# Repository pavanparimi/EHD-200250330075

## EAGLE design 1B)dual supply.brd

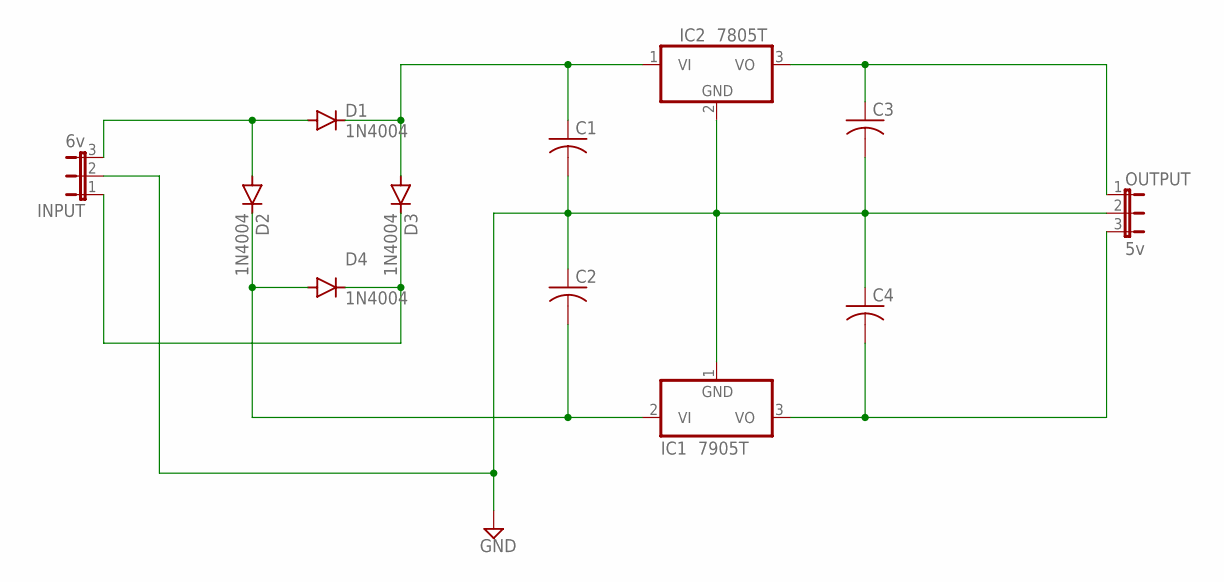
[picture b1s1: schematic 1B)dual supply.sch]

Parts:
C1, C2, C3, C4: C-US150-054X183; C150-054X183
D1, D2, D3, D4: 1N4004; DO41-10
IC1: 7905T; TO220H
IC2: 7805T; TO220H
INPUT: 6v; JP2
OUTPUT: 5v; JP2

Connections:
GND: C1.2, C2.1, C3.2, C4.1, IC1.1 (GND), IC2.2 (GND), INPUT.2, OUTPUT.2
unnamed: D1.A, D2.A, INPUT.3
unnamed: C2.2, D2.C, D4.A, IC1.2 (VI)
unnamed: D3.C, D4.C, INPUT.1
unnamed: C1.1, D1.C, D3.A, IC2.1 (VI)
unnamed: C4.2, IC1.3 (VO), OUTPUT.3
unnamed: C3.1, IC2.3 (VO), OUTPUT.1

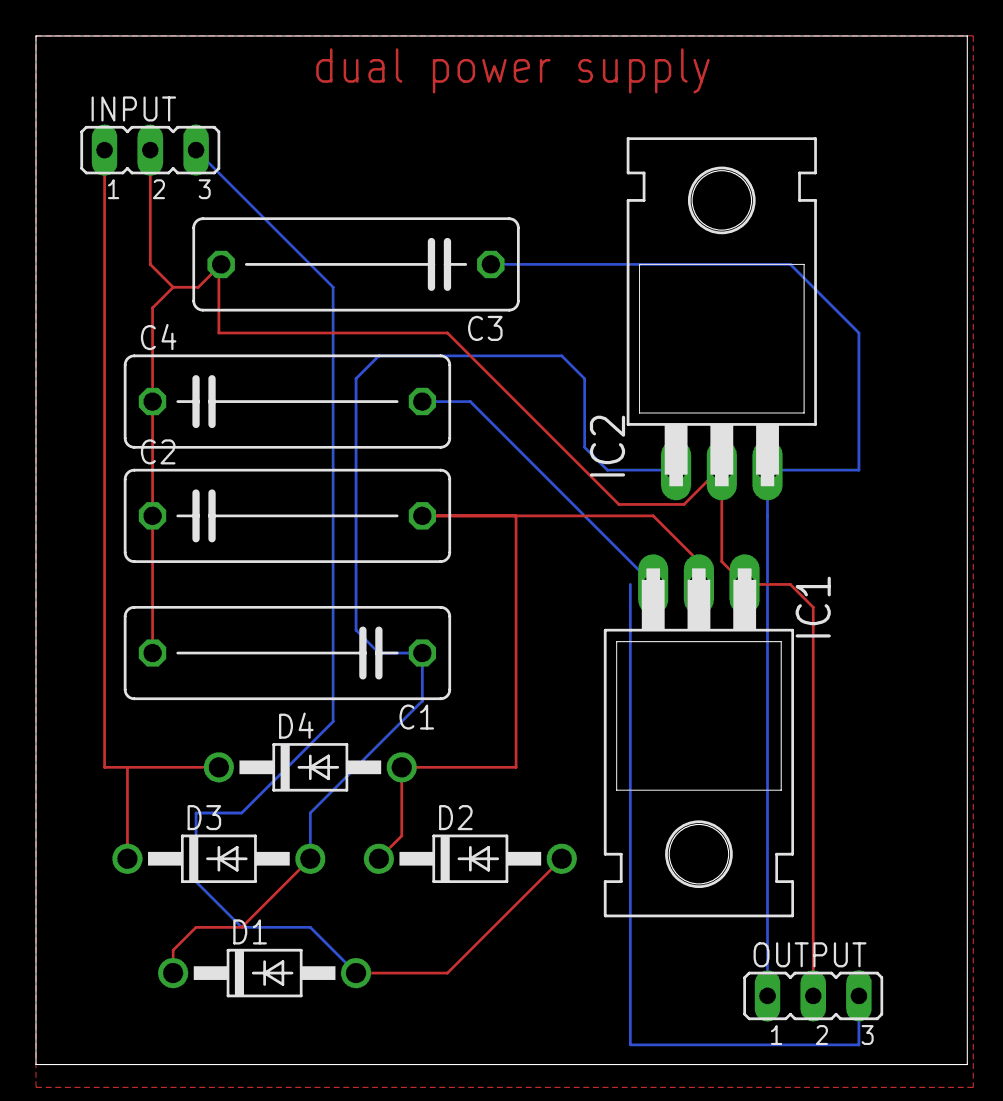
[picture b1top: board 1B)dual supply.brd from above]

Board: 2 copper layers, 51.7 x 57.1 mm, 12 parts (0 on the bottom side), 7 nets.

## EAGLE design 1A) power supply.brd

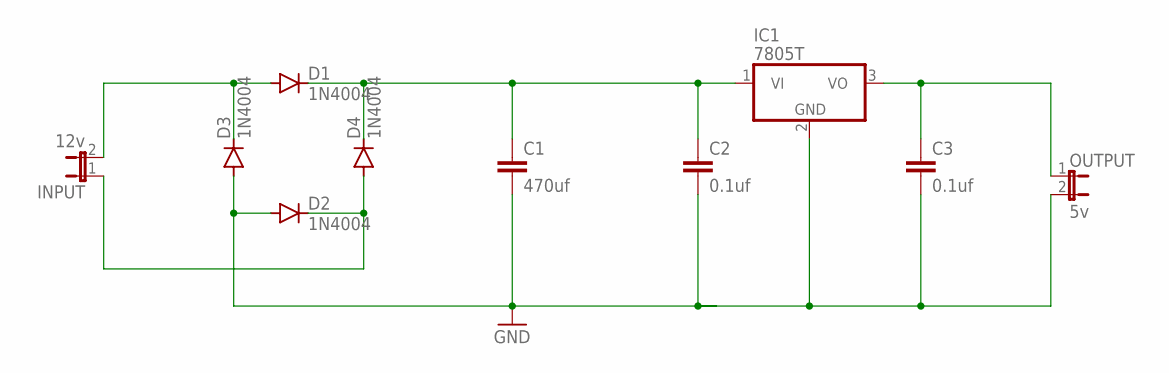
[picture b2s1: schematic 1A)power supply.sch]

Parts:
C1: 470uf; C2.5-2
C2, C3: 0.1uf; C2.5-2
D1, D2, D3, D4: 1N4004; DO41-10
IC1: 7805T; TO220H
INPUT: 12v; JP1
OUTPUT: 5v; JP1

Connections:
GND: C1.2, C2.2, C3.2, D2.A, D3.A, IC1.2 (GND), OUTPUT.2
unnamed: D1.A, D3.C, INPUT.2
unnamed: D2.C, D4.A, INPUT.1
unnamed: C1.1, C2.1, D1.C, D4.C, IC1.1 (VI)
unnamed: C3.1, IC1.3 (VO), OUTPUT.1

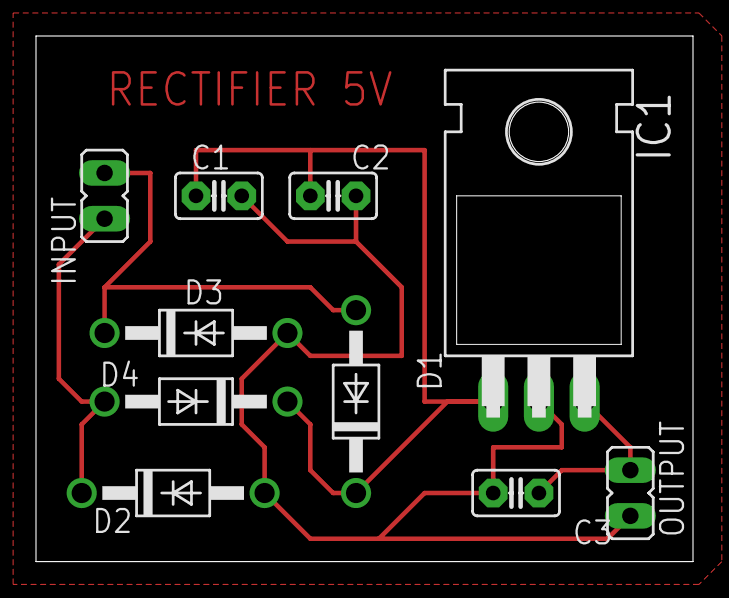
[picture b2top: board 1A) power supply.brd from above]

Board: 2 copper layers, 36.5 x 29.2 mm, 10 parts (0 on the bottom side), 5 nets.
